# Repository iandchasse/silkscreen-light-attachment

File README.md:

# Silkscreen light attachment

> [!IMPORTANT]
> **AI-generated design. This is an accessory, not part of the Silkscreen PCBA.**
>
> This light attachment was designed with substantial AI assistance: its board and housing are generated by code
> written with AI tools. It serves two purposes: a test of what AI tools can and cannot do with a simple electrical
> design like an LED strip, and a functional accessory for the base Silkscreen PCBA. The Silkscreen PCBA itself
> ([silkscreen-pcb](https://github.com/iandchasse/silkscreen-pcb)) was not AI-generated.
>
> See Silkscreen's AI disclosure: https://silkscreenreader.com/ai

**A clip-on warm/cool reading light for the [Silkscreen](https://github.com/iandchasse/silkscreen-pcb) e-reader.** It is a small cap that pushes onto the top of the stock case. Three header pins go down through the opening the case already has in its top wall and plug into the main board's expansion header, the 12-pin socket on its top edge (labelled `J6` on the board). The case is not modified.

- A 1.0 mm board carries 5 warm (3000 K) and 5 cool (6000 K) LEDs and two 200 Ω resistors. JLCPCB assembles those 12 parts, and can also fit the two short through-hole pin headers; or you solder the headers yourself (3 joints).
- Two printed parts (base + lid) and two M2 screws hold the board. No glue, no optics parts, nothing to modify.
- The reader's normal frontlight controls (brightness and warmth) drive it. It is meant for a reader with nothing in the main board's frontlight connector (no panel frontlight and no light strip).

> **Status (2026-10-21): the rev B board and the rev B housing are built and work.** Pins line up with the expansion header, the cap fits the 4.26" case and snaps on, and the light works. **The rev C housing (enclosing hood, rounder brow, rabbeted seam) is checked in CAD only and has not been printed yet.** The board is unchanged (rev B). The rev B prints are in `archive/rev-B-housing/print/`.
>
> Cheapest first step: print the two parts (about 36 min, 8.6 g; rev C, with the enclosing hood) and try the empty base on your case. It has no metal, so that is safe.

| On the stock case (render) | Exploded | Light board, LED side (faces the case) |
|:---:|:---:|:---:|
|  |  |  |

More renders: [front](housing/out/render/front.png), [right side](housing/out/render/side_right.png), [section through the expansion header](housing/out/render/section_J6_x54.66.png), [section through an LED](housing/out/render/section_led_x28.1.png), [section through a screw boss](housing/out/render/section_boss_x10.png), [board top side](pcb/docs/images/render_bottom.png).

## What you need

LCSC stock on 2026-09-25 is in parentheses. All five parts are JLC Extended parts.

| Item | Qty | Notes |
|---|---|---|
| Light PCBA | 1 | 2 layers, 1.0 mm, 65.0 × 17.0 mm. Everything sits on one side. The JLC files hold all 14 parts: the 12 SMD parts plus the 2 headers (through-hole; untick them at JLC to solder them yourself): warm LED C210340 × 5 (102,969), cool LED C210343 × 5 (40,519), 200 Ω Vishay CRCW0805200RFKEAHP C5972814 × 2 (2,477). See [ORDERING](docs/ORDERING.md) |
| Pin header, 1 × 2 (`J1` in the BOM) | 1 | Hong Cheng HC-PZ254-11.5L-1x2PZ, LCSC [C27985187](https://www.lcsc.com/product-detail/pin-headers_hong-cheng-hc-pz254-11-5l-1x2pz_C27985187.html) (24,852). Fitted by JLC or by you |
| Pin header, 1 × 1 (`J2` in the BOM) | 1 | Hong Cheng HC-PZ254-11.5L-1x1PZ, LCSC [C27985186](https://www.lcsc.com/product-detail/pin-headers_hong-cheng-hc-pz254-11-5l-1x1pz_C27985186.html) (10,775). Fitted by JLC or by you |
| Printed base and lid | 1 each | PETG (PLA for a trial), no supports. Base 20 min 20 s, 3.25 g; lid 15 min 50 s, 5.32 g (Elegoo CC2, 0.4 nozzle, 0.20 mm). **Print the lid in a light colour (white, light grey, silver silk):** the hood is a reflector, and a black lid absorbs the light it would add. Optional: turn on **Detect thin wall** so the 0.2 mm stop under each screw hole prints |
| Screws, M2 × 3 pan head | 2 | ISO 7045 (cross) or ISO 14583 (Torx), machine or thread-forming. **Not longer than 3 mm** |

Tools: a soldering iron, a spare 2.54 mm 2-row female header (a jig to hold the pins square), a small screwdriver and a multimeter. A current-limited bench supply is useful for the optional bench test.

## How it goes together

1. Order the boards with assembly, and print the base and lid ([ORDERING](docs/ORDERING.md)).
2. If JLC did not fit them, solder the two pin headers straight, using the female header as a jig. The pin tails stay full length: the lid has a pocket for them.
3. Drop the board into the base, put the lid on and drive the 2 screws until snug.
4. Turn the frontlight **off**, push the cap straight down onto the top of the reader, and take it off by its ends.

Full steps: [ASSEMBLY](docs/ASSEMBLY.md).

## Safety in short

- **Frontlight off (brightness 0) before you plug it in or pull it off.** If the light was on with nothing attached, wait about 10 s.
- **Only the expansion header's pins 5, 6 and 11 are used.** Every other position has no pin, pad or copper on the board, so the ground pin (4) and the raw battery pin (12) are never touched.
- **The cap keys the plug.** The case opening is off-centre, and the cap's walls line the pins up before they reach the expansion header. Turned round, the pins land on the solid top of the case.
- **Never plug the bare board into the expansion header.** Rev B has no reverse-protection diodes. The main board is safe either way, but a wrongly placed bare board can put a reverse voltage across the LEDs and damage them.
- **TPS923611 main boards** have a smaller hot-plug margin, so the light-off rule matters most there.

Details and the bench test: [SAFETY-AND-TEST](docs/SAFETY-AND-TEST.md).

## What the light is like

Bright near the top of the page and fading down it: 10 mm down the page gets about 12 × the light of the page middle, the bottom edge about 1/5 of it. Fine as a reading light, not an even frontlight. The front hood hides the LEDs and the board edge from your eyes and, on a light-coloured lid, bounces a little more light down the page (about +12 % in the lower half, +14 % mid-page, +24 % at the top; none on a black lid). Shaping the light further is a job for printed changes to the cap. Numbers: [DESIGN](docs/DESIGN.md#optics-functional-enough).

## Docs

| Doc | What it covers |
|---|---|
| [docs/ORDERING.md](docs/ORDERING.md) | JLCPCB PCB and assembly fields, the placement-preview check, headers, screws, printing |
| [docs/ASSEMBLY.md](docs/ASSEMBLY.md) | Soldering the headers, putting the cap together, fitting it on the reader |
| [docs/SAFETY-AND-TEST.md](docs/SAFETY-AND-TEST.md) | The rules, a bench test of the bare board, what the reader should show |
| [docs/DESIGN.md](docs/DESIGN.md) | Why it is built this way, electrical and optics numbers, known limits |
| [docs/FIRMWARE-NOTES.md](docs/FIRMWARE-NOTES.md) | Recommended firmware changes (enable pulse, load check). The firmware is not changed |
| [pcb/docs/jlc-notes.md](pcb/docs/jlc-notes.md) | Generated JLC order notes |
| [pcb/docs/design_summary.md](pcb/docs/design_summary.md) | Generated electrical and placement summary |
| [housing/out/REPORT.md](housing/out/REPORT.md) | Generated housing check report |
| [design/DESIGN-SPEC-revB.md](design/DESIGN-SPEC-revB.md) | The rev B contract |

## Folder map

| Path | What it is |
|---|---|
| `pcb/` | Generated KiCad 9 project. `pcb/tools/` generates everything; do not edit the `.kicad_*` files by hand |
| `pcb/production/` | Gerber zip, `bom.csv`, `jlc_bom.csv`, `jlc_cpl.csv`, STEP/STL (including the PCBA in the case frame) |
| `pcb/docs/` | Schematic and layout PDFs, renders, `design_summary.md`, `jlc-notes.md`, gate reports, part evidence |
| `housing/src/` | CadQuery source for the base and lid, and the fit checks |
| `housing/out/` | Print files (`print/base.stl`, `lid.stl`, `.step`, `plate.3mf`), `REPORT.md`, `checks.json`, renders, slicer report |
| `design/` | The rev B contract (`DESIGN-SPEC-revB.md`), the stock-case mechanical spec, and the rev A design notes and reviews |
| `research/` | Source research: the expansion header (`J6`), electrical and mechanical, and the stock case |
| `tools/` | Optics ray-trace scripts (`optics_sim.py` is the one rev B uses; the rev A rod-lens scripts are in `archive/rev-A-rod-lens/tools/`) |
| `workflows/` | **Local only, not tracked**: the scripts that drove the design runs |
| `archive/rev-A-rod-lens/` | Rev A (rod lens, carrier, clip and cover): its PCB, housing and docs. Not current |
| `archive/rev-B-housing/print/` | The rev B printed parts (the ones first printed: short visor, open ends, flat seam). Superseded by the rev C housing in `housing/out/print/` |
| `enclosures/silkscreen-enclosure-claude/` | **Local only, not tracked**: the old rev K case copy. The checks now read the consolidated 4.26" case instead (see Housing below) |

## Regenerating

**PCB.** Close KiCad first: the scripts refuse to write while a `*.lck` file exists.

```
cd pcb
"C:\Program Files\KiCad\9.0\bin\python.exe" tools\generate.py
"C:\Program Files\KiCad\9.0\bin\python.exe" tools\make_outputs.py
```

`make_outputs.py` runs every gate first and writes `production/`, `docs/` and `build/geometry.json` only if all pass.

**Housing.** Use a Python 3.11 venv made from silkscreen-enclosures' `enclosures/case-426/requirements.txt` (CadQuery, trimesh, manifold3d). Run the PCB step first: the housing reads `pcb/build/geometry.json` and the case it fits: the **4.26" standard (strip-less) case**, whose tub.stl + lid.stl are copied into `housing/reference/case-426-standard/` (from silkscreen-enclosures, `enclosures/case-426/out/standard/`; see `PROVENANCE.md` there). Set `SILKSCREEN_CASE_OUT` to check against another build, e.g. a fresh one in `../silkscreen-enclosures/enclosures/case-426/out/standard/`. The 3.68" reader's trimmed board has no expansion header, so it is not supported.

```
cd housing
python src\build.py       # --no-render for a quicker run
```

`build.py` builds both parts, runs the checks, writes `out/` and exits with code 1 on any failed check. Optional: `python src\optics_report.py` (system Python) refreshes `out/optics.json`, and `src\slice_check.py` (same venv, needs OrcaSlicer) refreshes the slice report; run `build.py` again afterwards to fold both into `REPORT.md`.

## Credits and licence

Designed by Ian Chasse (idc LLC) as a companion to [silkscreen-pcb](https://github.com/iandchasse/silkscreen-pcb). The generator structure comes from the sibling project [silkscreen-light-strip](https://github.com/iandchasse/silkscreen-light-strip). The stock case is the 4.26" case of [silkscreen-enclosures](https://github.com/iandchasse/silkscreen-enclosures) (its top is unchanged since rev K).

CERN-OHL-S-2.0, © 2026 idc LLC. See [LICENSE](LICENSE) and [NOTICE](NOTICE). The KiCad library parts in `pcb/lib/` keep their own terms (listed in NOTICE). The third-party evidence behind the part choices (a datasheet page, LCSC/EasyEDA part data) is kept locally in `pcb/docs/sources/` and is not published.

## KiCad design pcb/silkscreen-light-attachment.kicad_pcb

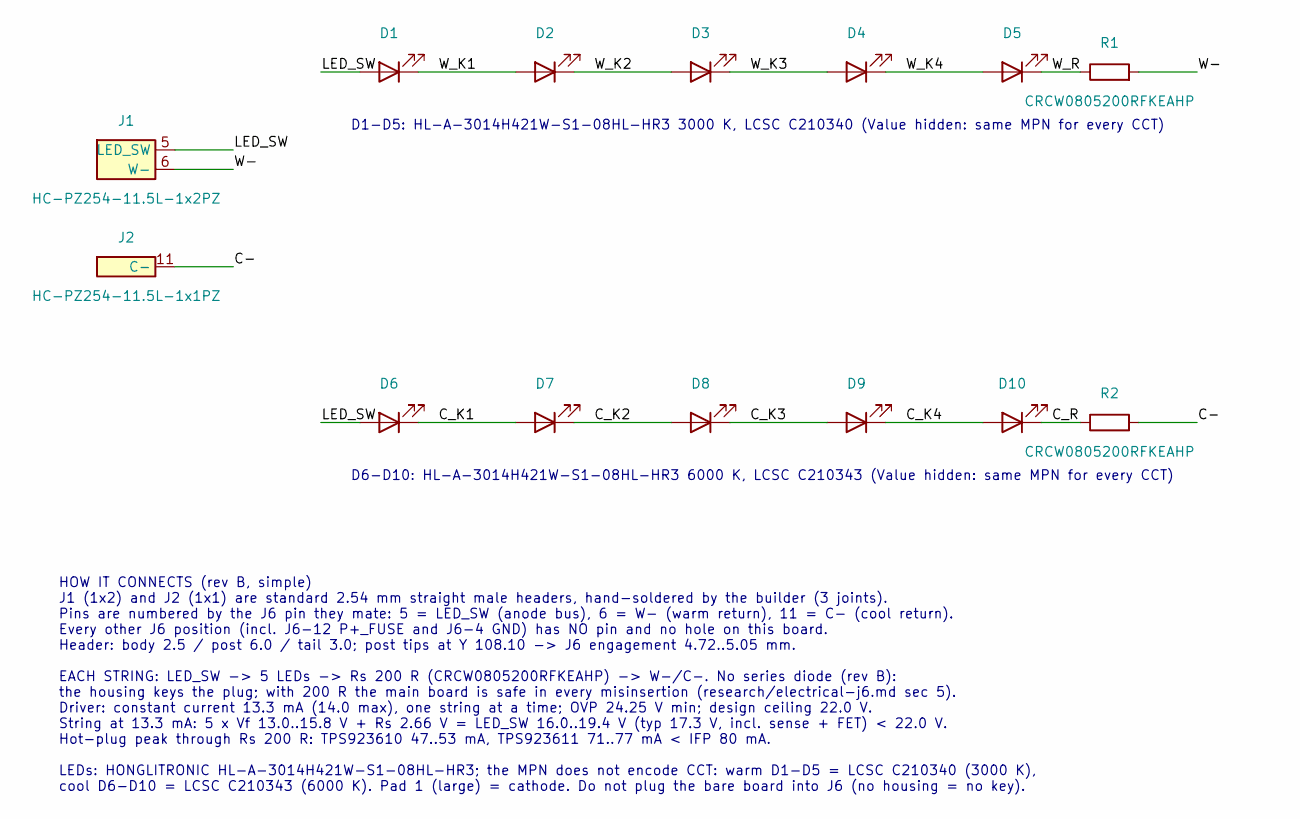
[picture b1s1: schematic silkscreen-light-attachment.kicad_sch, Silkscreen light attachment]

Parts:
D1, D2, D3, D4, D5, D6, D7, D8, D9, D10: HL-A-3014H421W-S1-08HL-HR3; LED_3014_HONGLI_HL-A-3014H421W; MPN HL-A-3014H421W-S1-08HL-HR3; DigiKey n/a - LCSC only (C210340 warm / C210343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
J1: HC-PZ254-11.5L-1x2PZ; J6_PLUG_1x2_P5_P6; MPN HC-PZ254-11.5L-1x2PZ; DigiKey Harwin M20-9990246 (DigiKey product 372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
J2: HC-PZ254-11.5L-1x1PZ; J6_PLUG_1x1_P11; MPN HC-PZ254-11.5L-1x1PZ; DigiKey 1 pin cut from Harwin M20-9990246 (Digi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
R1, R2: CRCW0805200RFKEAHP; R_0805_2012Metric; MPN CRCW0805200RFKEAHP; DigiKey 541-CRCW0805200RFKEAHPCT-ND

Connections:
/C-: J2.11, R2.2
/C_K1: D6.1 (K), D7.2 (A)
/C_K2: D7.1 (K), D8.2 (A)
/C_K3: D8.1 (K), D9.2 (A)
/C_K4: D9.1 (K), D10.2 (A)
/C_R: D10.1 (K), R2.1
/LED_SW: D1.2 (A), D6.2 (A), J1.5 (LED_SW)
/W-: J1.6 (W-), R1.2
/W_K1: D1.1 (K), D2.2 (A)
/W_K2: D2.1 (K), D3.2 (A)
/W_K3: D3.1 (K), D4.2 (A)
/W_K4: D4.1 (K), D5.2 (A)
/W_R: D5.1 (K), R1.1

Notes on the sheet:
D1-D5: HL-A-3014H421W-S1-08HL-HR3 3000 K, LCSC C210340 (Value hidden: same MPN for every CCT)
D6-D10: HL-A-3014H421W-S1-08HL-HR3 6000 K, LCSC C210343 (Value hidden: same MPN for every CCT)
HOW IT CONNECTS (rev B, simple) J1 (1x2) and J2 (1x1) are standard 2.54 mm straight male headers, hand-soldered by the builder (3 joints). Pins are numbered by the J6 pin they mate: 5 = LED_SW (anode bus), 6 = W- (warm return), 11 = C- (cool return). Every other J6 position (incl. J6-12 P+_FUSE and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

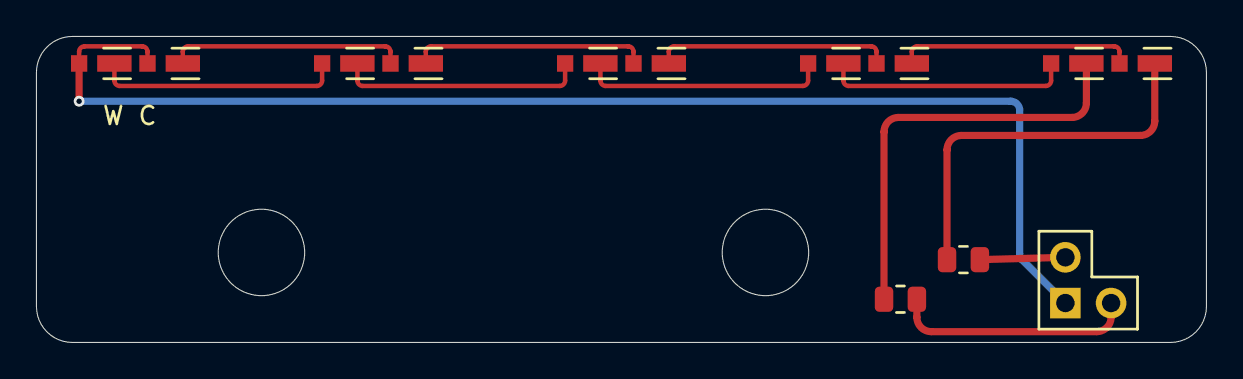
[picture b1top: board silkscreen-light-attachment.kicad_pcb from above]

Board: 2 copper layers, 65.0 x 17.0 mm, 16 parts (0 on the bottom side), 13 nets.

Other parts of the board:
H1: M1 housing boss (dia 4.40) + ST2.2 screw; NPTH_4.80mm
H2: M2 housing boss (dia 4.40) + ST2.2 screw; NPTH_4.80mm

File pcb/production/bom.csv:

Qty,Refs,Value,Manufacturer,MPN,DigiKey,LCSC,JLC type,Footprint,Assembly,Description
5,"D1,D2,D3,D4,D5",HL-A-3014H421W-S1-08HL-HR3,HONGLITRONIC,HL-A-3014H421W-S1-08HL-HR3,n/a - LCSC only (C210340 warm / C210343 cool),C210340,JLC Extended,LED_3014_HONGLI_HL-A-3014H421W,JLC SMT (F side),"Warm white LED 3000 K (bin WS 2800-3100 K), LCSC C210340; 3014 top view 3.0x1.4x0.7; the MPN is shared by every CCT - order by the LCSC code"
5,"D6,D7,D8,D9,D10",HL-A-3014H421W-S1-08HL-HR3,HONGLITRONIC,HL-A-3014H421W-S1-08HL-HR3,n/a - LCSC only (C210340 warm / C210343 cool),C210343,JLC Extended,LED_3014_HONGLI_HL-A-3014H421W,JLC SMT (F side),"Cool white LED 6000 K (bin 60-5 5700-6500 K), LCSC C210343; 3014 top view 3.0x1.4x0.7; the MPN is shared by every CCT - order by the LCSC code"
1,J1,HC-PZ254-11.5L-1x2PZ,Hong Cheng,HC-PZ254-11.5L-1x2PZ,Harwin M20-9990246 (DigiKey product 3728226) - 6.1 mm post,C27985187,JLC Extended,J6_PLUG_1x2_P5_P6,"THT: JLC hand-solders it, or untick it at JLC and solder it yourself","1x2 2.54 mm straight male pin header, body 2.5, mating post 6.0, tail 3.0, 0.64 sq; body on the LED side, soldered by the builder on the plain side; pins = J6 5/6"
1,J2,HC-PZ254-11.5L-1x1PZ,Hong Cheng,HC-PZ254-11.5L-1x1PZ,1 pin cut from Harwin M20-9990246 (DigiKey product 3728226),C27985186,JLC Extended,J6_PLUG_1x1_P11,"THT: JLC hand-solders it, or untick it at JLC and solder it yourself","1x1 2.54 mm straight male pin header, body 2.5, mating post 6.0, tail 3.0, 0.64 sq; body on the LED side, soldered by the builder on the plain side; pins = J6 11"
2,"R1,R2",CRCW0805200RFKEAHP,Vishay Dale,CRCW0805200RFKEAHP,541-CRCW0805200RFKEAHPCT-ND,C5972814,JLC Extended,R_0805_2012Metric,JLC SMT (F side),200 R 1 % 0.5 W pulse-proof thick film 0805 (CRCW-HP); string series resistor

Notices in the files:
pcb/silkscreen-light-attachment.kicad_pcb:
Licensed under CERN-OHL-S-2.0
(c) 2026 idc LLC
